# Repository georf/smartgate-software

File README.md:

Dieses Projekt soll vorhandene Chamberlain-Motoren für eine Hofeinfahrt steuern. Die Platine ist mit KiCad gestaltet. Der Code lässt das Tor über MQTT, Taster und 433MHz-Modul steuern.

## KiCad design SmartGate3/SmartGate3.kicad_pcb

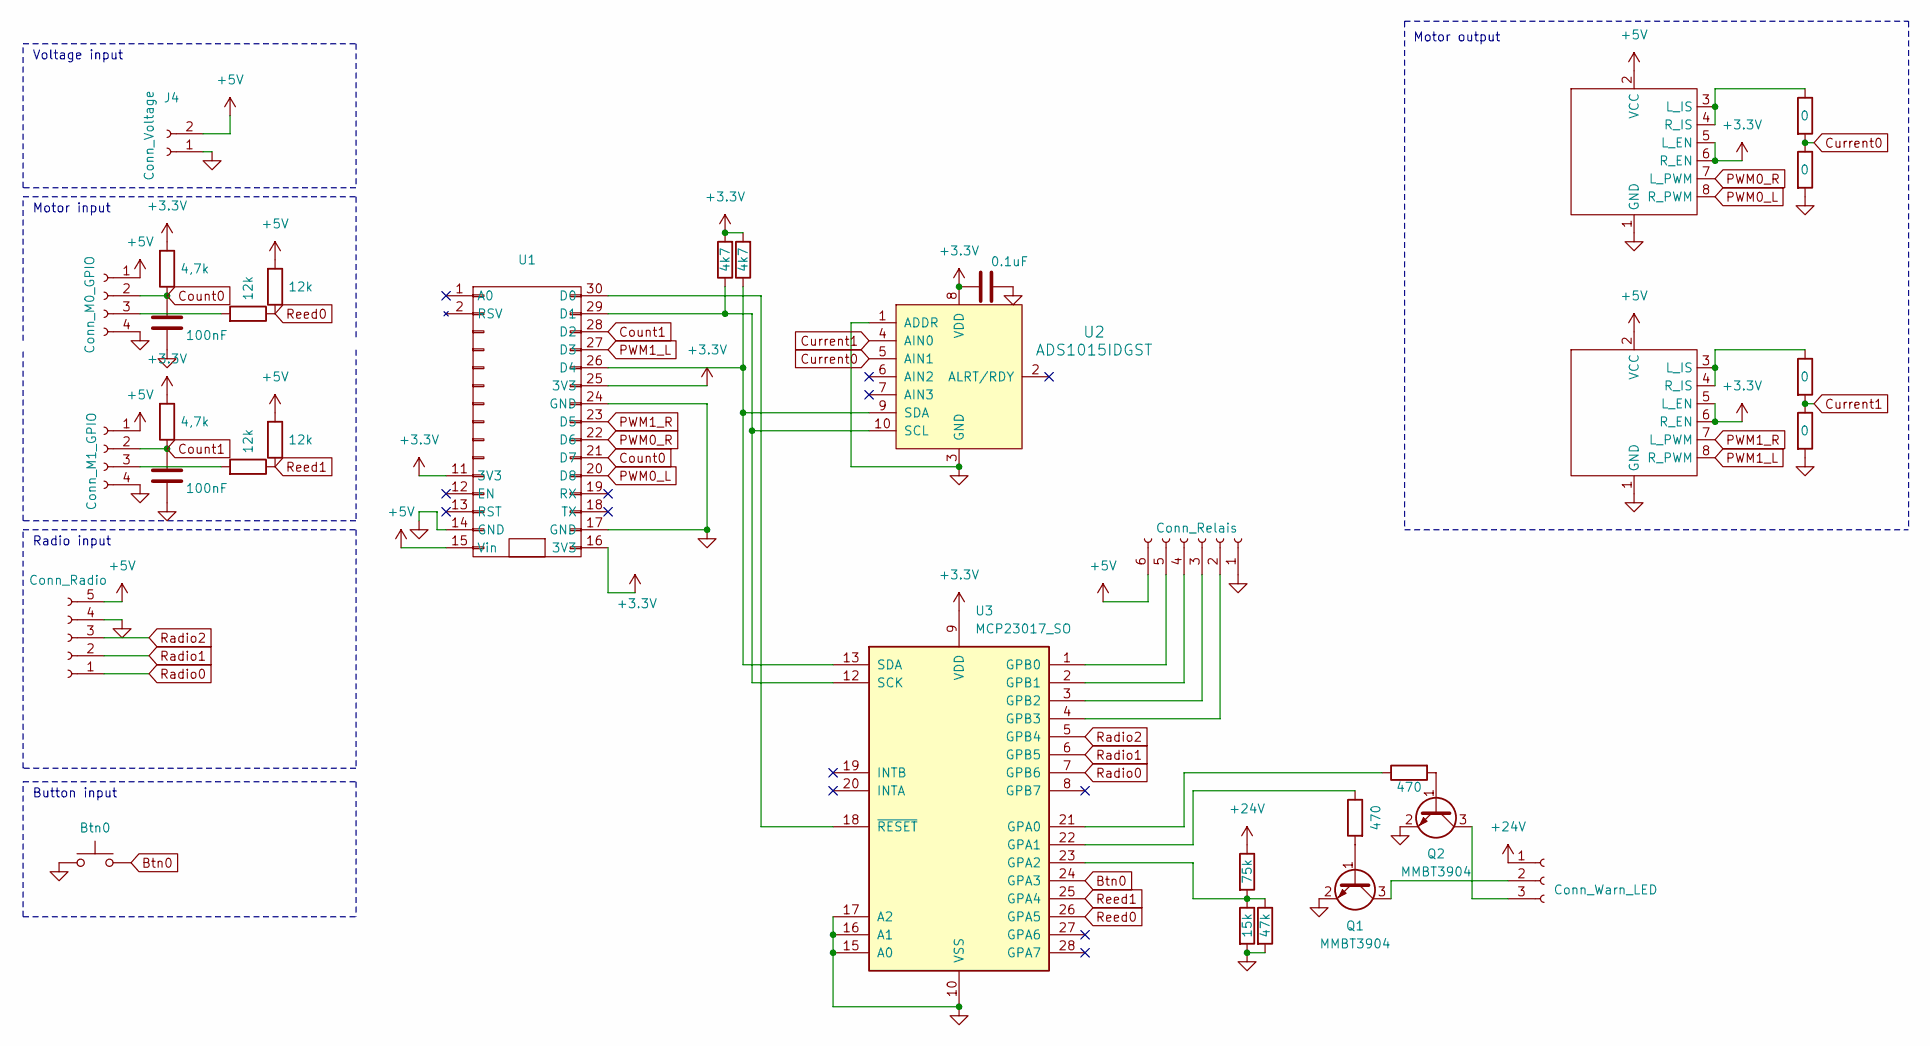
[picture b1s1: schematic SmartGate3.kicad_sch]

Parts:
C1: 0.1uF; R_1206_3216Metric_Pad1.30x1.75mm_HandSolder
C2, C3: 100nF; R_1206_3216Metric_Pad1.30x1.75mm_HandSolder
J1: Conn_Radio; TerminalBlock_Phoenix_PT-1,5-5-5.0-H_1x05_P5.00mm_Horizontal
J2: Conn_M0_GPIO; TerminalBlock_Phoenix_PT-1,5-4-5.0-H_1x04_P5.00mm_Horizontal
J3: Conn_M1_GPIO; TerminalBlock_Phoenix_PT-1,5-4-5.0-H_1x04_P5.00mm_Horizontal
J4: Conn_Voltage; TerminalBlock_Phoenix_PT-1,5-2-5.0-H_1x02_P5.00mm_Horizontal
J5: Conn_Relais; PinHeader_1x06_P2.54mm_Vertical
J6: Conn_Warn_LED; TerminalBlock_Phoenix_PT-1,5-3-5.0-H_1x03_P5.00mm_Horizontal
Q1, Q2: MMBT3904; SOT-23
R1, R2, R3, R4: 12k; R_1206_3216Metric_Pad1.30x1.75mm_HandSolder
R5, R6: 4k7; R_1206_3216Metric_Pad1.30x1.75mm_HandSolder
R7: 75k; R_1206_3216Metric_Pad1.30x1.75mm_HandSolder
R8: 15k; R_1206_3216Metric_Pad1.30x1.75mm_HandSolder
R9, R10: 470; R_1206_3216Metric_Pad1.30x1.75mm_HandSolder
R11, R12, R13, R14: 0; R_1206_3216Metric_Pad1.30x1.75mm_HandSolder
R15: 47k; R_1206_3216Metric_Pad1.30x1.75mm_HandSolder
R16, R17: 4,7k; R_1206_3216Metric_Pad1.30x1.75mm_HandSolder
SW1: Btn0; TerminalBlock_Phoenix_PT-1,5-2-5.0-H_1x02_P5.00mm_Horizontal
U1: NodeMCU ESP8266 weniger Pins
U2: ADS1015IDGST; ADS1015-Platine; MPN ADS1015IDGST; Digi-Key_PN 296-25227-1-ND
U3: MCP23017_SO; SOIC-28W_7.5x17.9mm_P1.27mm
U4, U5: PinHeader_2x04_P2.54mm_Vertical

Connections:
+3.3V: C1.1, R5.2, R6.2, R16.2, R17.2, U1.11 (3V3), U1.16 (3V3), U1.25 (3V3), U2.8 (VDD), U3.9 (VDD), U4.5 (L_EN), U4.6 (R_EN), U5.5 (L_EN), U5.6 (R_EN)
+5V: J1.5, J2.1, J3.1, J4.2, J5.6, R3.2, R4.2, U1.15 (Vin), U4.2 (VCC), U5.2 (VCC)
+24V: J6.1, R7.1
Btn0: SW1.1, U3.24 (GPA3)
Count0: C2.2, J2.2, R16.1, U1.21 (D7)
Count1: C3.2, J3.2, R17.1, U1.28 (D2)
Current0: R11.2, R12.1, U2.5 (AIN1)
Current1: R13.2, R14.1, U2.4 (AIN0)
GND: C1.2, C2.1, C3.1, J1.4, J2.4, J3.4, J4.1, J5.1, Q1.2 (E), Q2.2 (E), R8.2, R12.2, R14.2, R15.2, SW1.2, U1.14 (GND), U1.17 (GND), U1.24 (GND), U2.1 (ADDR), U2.3 (GND), U3.10 (VSS), U3.15 (A0), U3.16 (A1), U3.17 (A2), U4.1 (GND), U5.1 (GND)
unnamed: J2.3, R1.2
unnamed: J3.3, R2.2
unnamed: J5.2, U3.4 (GPB3)
unnamed: J5.3, U3.3 (GPB2)
unnamed: J5.4, U3.2 (GPB1)
unnamed: J5.5, U3.1 (GPB0)
unnamed: J6.2, Q1.3 (C)
unnamed: J6.3, Q2.3 (C)
unnamed: Q1.1 (B), R9.2
unnamed: Q2.1 (B), R10.2
unnamed: U1.30 (D0), U3.18 (~RESET)
unnamed: R5.1, U1.29 (D1), U2.10 (SCL), U3.12 (SCK)
unnamed: R6.1, U1.26 (D4), U2.9 (SDA), U3.13 (SDA)
unnamed: R10.1, U3.21 (GPA0)
unnamed: R9.1, U3.22 (GPA1)
unnamed: R7.2, R8.1, R15.1, U3.23 (GPA2)
unnamed: R11.1, U4.3 (L_IS), U4.4 (R_IS)
unnamed: R13.1, U5.3 (L_IS), U5.4 (R_IS)
PWM0_L: U1.20 (D8), U4.8 (R_PWM)
PWM0_R: U1.22 (D6), U4.7 (L_PWM)
PWM1_L: U1.27 (D3), U5.8 (R_PWM)
PWM1_R: U1.23 (D5), U5.7 (L_PWM)
Radio0: J1.1, U3.7 (GPB6)
Radio1: J1.2, U3.6 (GPB5)
Radio2: J1.3, U3.5 (GPB4)
Reed0: R1.1, R3.1, U3.26 (GPA5)
Reed1: R2.1, R4.1, U3.25 (GPA4)

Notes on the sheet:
Motor input
Voltage input
Button input
Radio input
Motor output

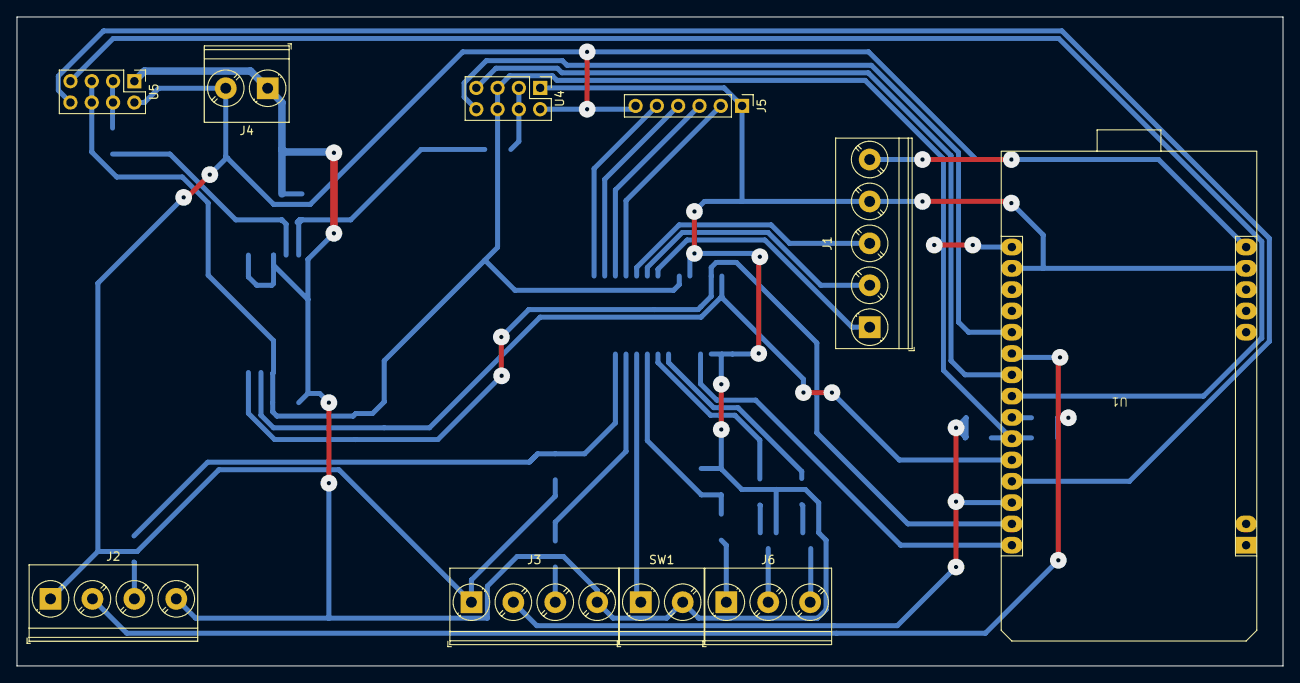
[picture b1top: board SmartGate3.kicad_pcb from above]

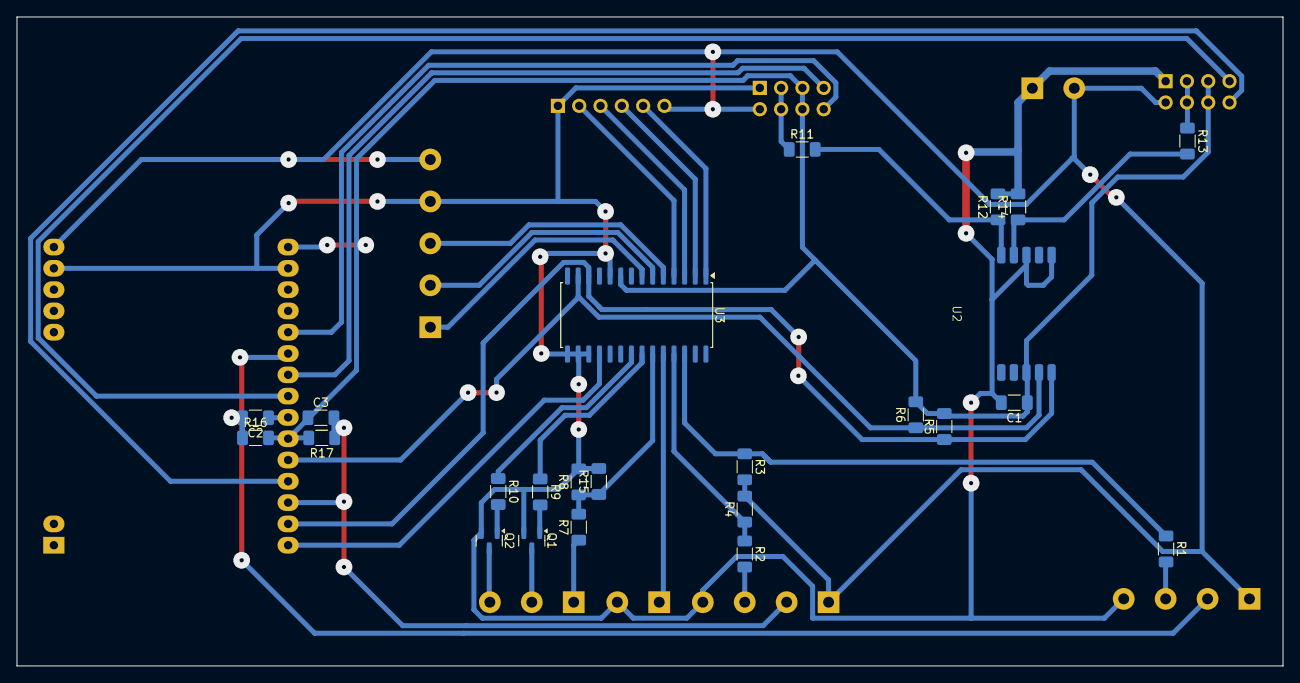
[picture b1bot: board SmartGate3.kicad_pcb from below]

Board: 2 copper layers, 151.0 x 77.4 mm, 34 parts (24 on the bottom side), 36 nets.

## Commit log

2023-02-04 Ohne Relais-Anschaltung
2023-02-04 Mit Relais-Anschaltung
2023-02-04 Feinjustierung
2024-02-18 ArduinoOTA einrichten
2024-02-18 MQTT für Homeassistant optimieren
2024-12-16 Fix steps in Code
2025-10-05 Lauffähige Version
2026-01-25 Version 3
2026-01-25 KiCad-Projekt
2026-01-25 Add project description to README.md
2026-04-27 Änderungen im Interrupt besser schützen
2026-04-27 long-Overflow-Fehler verhindern
2026-04-27 Flügel-Einstellungen korrigieren
